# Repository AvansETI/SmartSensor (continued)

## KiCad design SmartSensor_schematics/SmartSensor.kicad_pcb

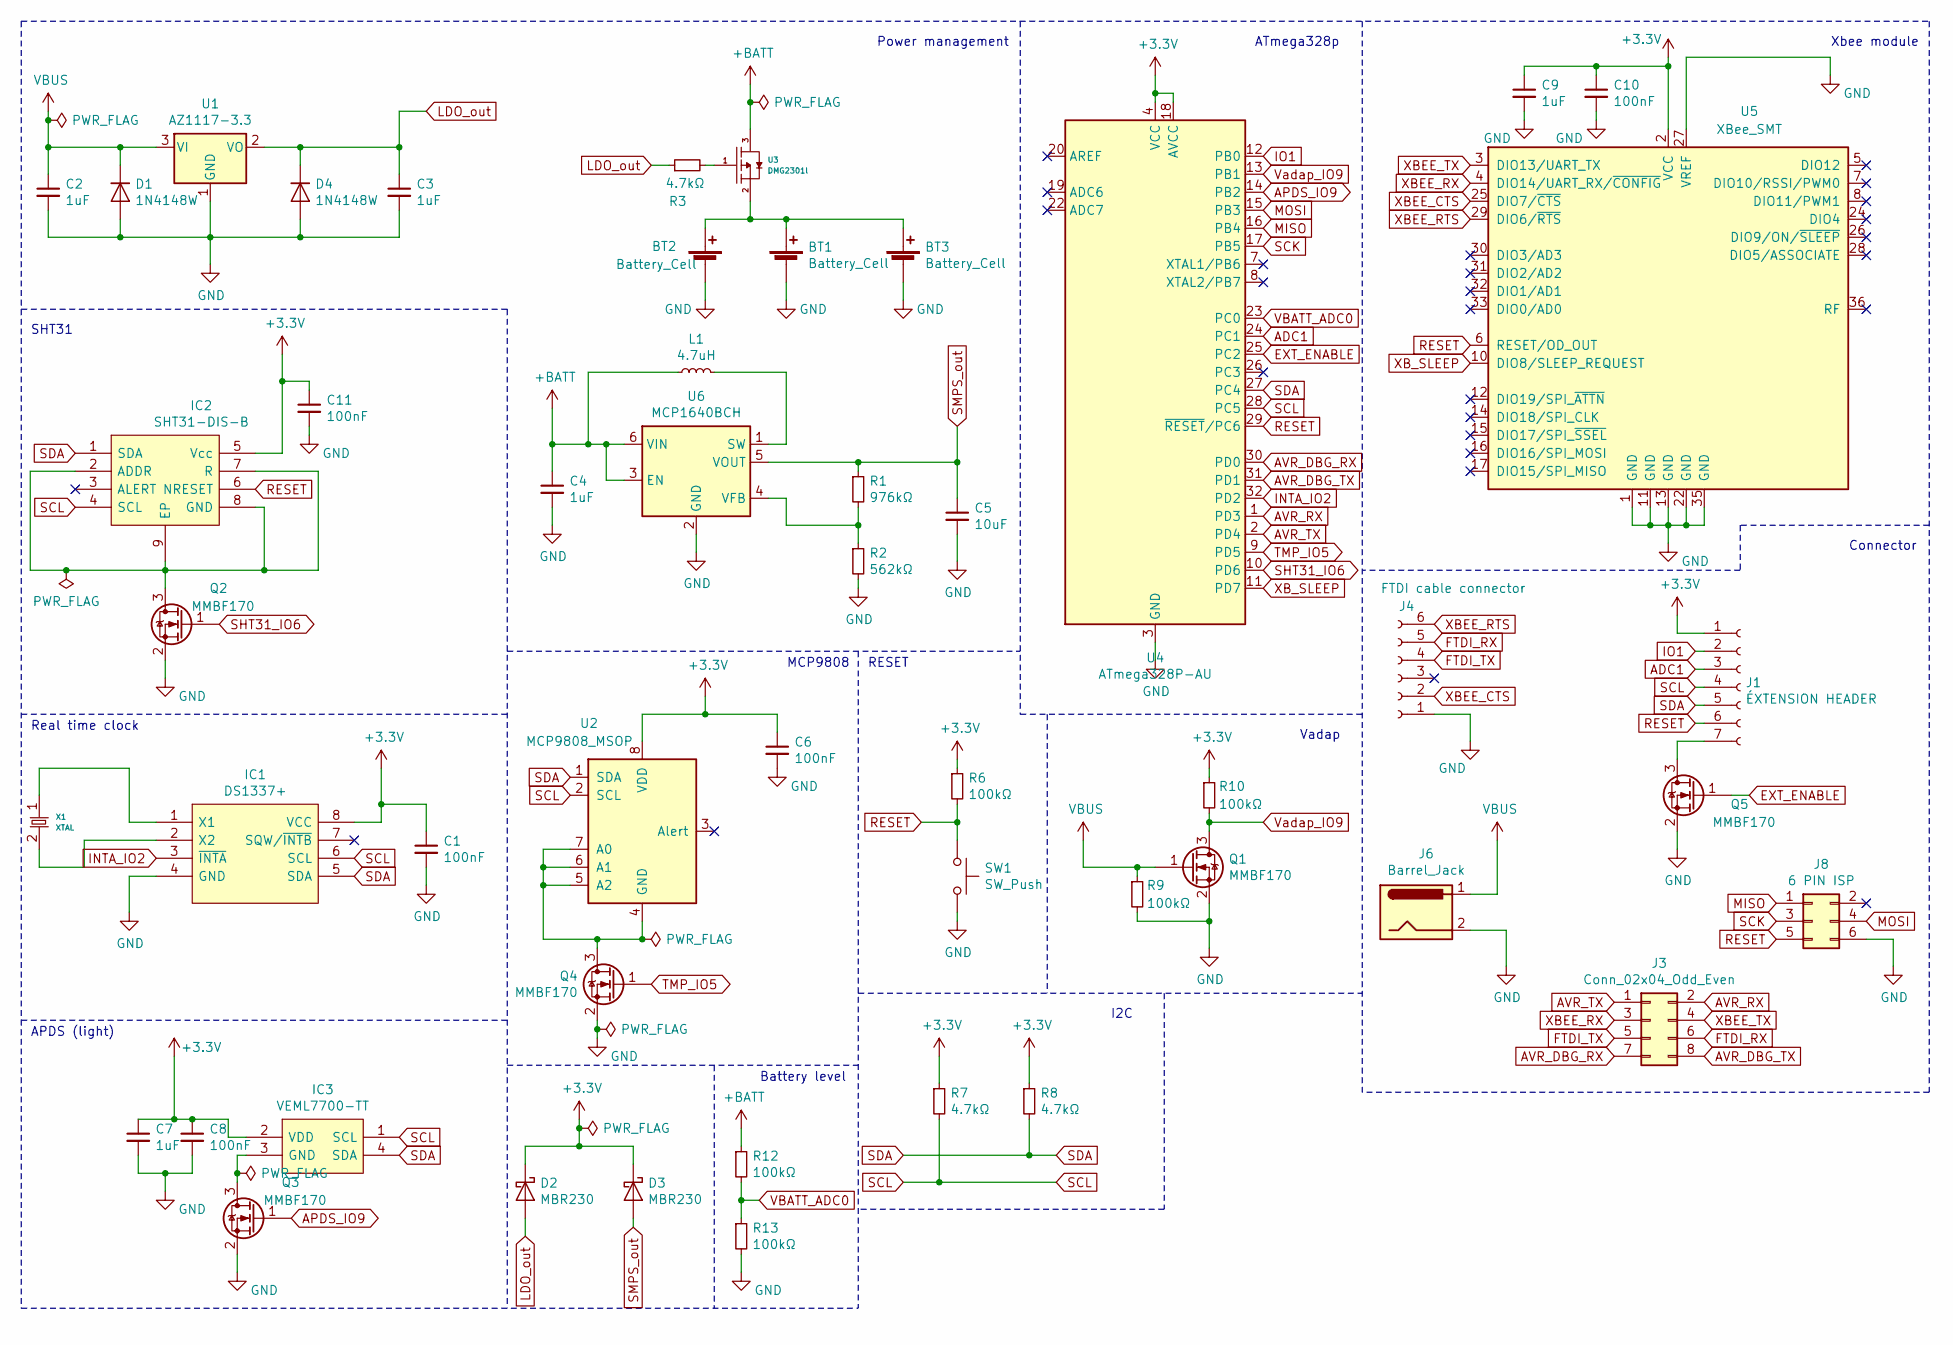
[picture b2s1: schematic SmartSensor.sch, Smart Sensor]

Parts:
BT1, BT2, BT3: Battery_Cell; 2460
C1, C6, C8, C10, C11: 100nF; C_1206_3216Metric_Pad1.42x1.75mm_HandSolder
C2, C3, C4, C7, C9: 1uF; C_1206_3216Metric_Pad1.42x1.75mm_HandSolder
C5: 10uF; C_1206_3216Metric_Pad1.42x1.75mm_HandSolder
D1, D4: 1N4148W; D_SOD-123
D2, D3: MBR230; D_SOD-123F
IC1: DS1337+; DIP794W56P254L938H457Q8N; Manufacturer_Part_Number DS1337+; Mouser Part Number 700-DS1337
IC2: SHT31-DIS-B; SON50P250X250X90-9N-D; Mouser Part Number 403-SHT31-DIS-B
IC3: VEML7700-TT; VEML7700; Manufacturer_Part_Number VEML7700-TT; Mouser Part Number 78-VEML7700-TT
J1: ÉXTENSION HEADER; PinSocket_1x07_P2.54mm_Vertical
J3: Conn_02x04_Odd_Even; PinHeader_2x04_P2.54mm_Vertical
J4: FTDI cable connector; PinHeader_1x06_P2.54mm_Vertical
J6: Barrel_Jack; BarrelJack_Wuerth_6941xx301002
J8: 6 PIN ISP; PinHeader_2x03_P2.54mm_Vertical
L1: 4.7uH; L_Coilcraft_XxL4040
Q1, Q2, Q3, Q4, Q5: MMBF170; SOT-23
R1: 976kΩ; R_1206_3216Metric_Pad1.42x1.75mm_HandSolder
R2: 562kΩ; R_1206_3216Metric_Pad1.42x1.75mm_HandSolder
R3, R7, R8: 4.7kΩ; R_1206_3216Metric_Pad1.42x1.75mm_HandSolder
R6, R9, R10, R12, R13: 100kΩ; R_1206_3216Metric_Pad1.42x1.75mm_HandSolder
SW1: SW_Push; SW_PUSH_6mm
U1: AZ1117-3.3; SOT-223-3_TabPin2
U2: MCP9808_MSOP; MSOP-8_3x3mm_P0.65mm
U3: DMG2301l; SOT-23
U4: ATmega328P-AU; TQFP-32_7x7mm_P0.8mm
U5: XBee_SMT; Digi_XBee_SMT
U6: MCP1640BCH; SOT-23-6
X1: XTAL; Crystal_C38-LF_D3.0mm_L8.0mm_Vertical

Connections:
+3V3: C1.1, C6.1, C7.1, C8.1, C9.1, C10.1, C11.1, D2.1 (K), D3.1 (K), IC1.8 (VCC), IC2.5 (Vcc), IC3.2 (VDD), J1.1, R6.1, R7.1, R8.1, R10.1, U2.8 (VDD), U4.4 (VCC), U4.6 (VCC), U4.18 (AVCC), U5.2 (VCC); also elsewhere on the board
+BATT: C4.1, L1.1, R12.1, U3.3, U6.3 (EN), U6.6 (VIN)
APDS_IO9: Q3.1 (G), U4.14 (PB2); also elsewhere on the board
EXT_ENABLE: Q5.1 (G), U4.25 (PC2); also elsewhere on the board
GND: BT1.2 (-), BT2.2 (-), BT3.2 (-), C1.2, C2.2, C3.2, C4.2, C5.2, C6.2, C7.2, C8.2, C9.2, C10.2, C11.2, D1.2 (A), D4.2 (A), IC1.4 (GND), J4.1, J6.2, J8.6, Q1.2 (S), Q2.2 (S), Q3.2 (S), Q4.2 (S), Q5.2 (S), R2.2, R9.2, R13.2, SW1.2, U1.1 (GND), U4.3 (GND), U4.5 (GND), U4.21 (GND), U5.1 (GND), U5.11 (GND), U5.13 (GND), U5.22 (GND), U5.27 (VREF), U5.35 (GND), U6.2 (GND); also elsewhere on the board
INTA_IO2: IC1.3 (~INTA), U4.32 (PD2); also elsewhere on the board
LDO_out: C3.1, D2.2 (A), D4.1 (K), R3.1, U1.2 (VO)
MISO: J8.1, U4.16 (PB4); also elsewhere on the board
MOSI: J8.4, U4.15 (PB3); also elsewhere on the board
unnamed: BT1.1 (+), BT2.1 (+), BT3.1 (+), U3.2
unnamed: IC1.1 (X1), X1.1
unnamed: IC1.2 (X2), X1.2
unnamed: IC2.2 (ADDR), IC2.7 (R), IC2.8 (GND), IC2.9 (EP), Q2.3 (D)
unnamed: IC3.3 (GND), Q3.3 (D)
unnamed: J1.2, U4.12 (PB0)
unnamed: J1.3, U4.24 (PC1)
unnamed 26: J1.7, Q5.3 (D); also elsewhere on the board
unnamed: J3.1, U4.2 (PD4)
unnamed: J3.2, U4.1 (PD3)
unnamed: J3.5, J4.4
unnamed: J3.6, J4.5
unnamed: J3.7, U4.30 (PD0)
unnamed: J3.8, U4.31 (PD1)
unnamed: L1.2, U6.1 (SW)
unnamed: Q4.3 (D), U2.4 (GND), U2.5 (A2), U2.6 (A1), U2.7 (A0)
unnamed: R1.2, R2.1, U6.4 (VFB)
unnamed: R3.2, U3.1
RESET: IC2.6 (NRESET), J1.6, J8.5, R6.2, SW1.1, U4.29 (~RESET~/PC6), U5.6 (RESET/OD_OUT); also elsewhere on the board
SCK: J8.3, U4.17 (PB5); also elsewhere on the board
SCL: IC1.6 (SCL), IC2.4 (SCL), IC3.1 (SCL), J1.4, R7.2, U2.2 (SCL), U4.28 (PC5); also elsewhere on the board
SDA: IC1.5 (SDA), IC2.1 (SDA), IC3.4 (SDA), J1.5, R8.2, U2.1 (SDA), U4.27 (PC4); also elsewhere on the board
SHT31_IO6: Q2.1 (G), U4.10 (PD6); also elsewhere on the board
SMPS_out: C5.1, D3.2 (A), R1.1, U6.5 (VOUT)
TMP_IO5: Q4.1 (G), U4.9 (PD5); also elsewhere on the board
VBATT_ADC0: R12.2, R13.1, U4.23 (PC0); also elsewhere on the board
VBUS: C2.1, D1.1 (K), J6.1, Q1.1 (G), R9.1, U1.3 (VI)
Vadap_IO9: Q1.3 (D), R10.2, U4.13 (PB1); also elsewhere on the board
XBEE_CTS: J4.2, U5.25 (DIO7/~CTS); also elsewhere on the board
XBEE_RTS: J4.6, U5.29 (DIO6/~RTS); also elsewhere on the board
XBEE_RX: J3.3, U5.4 (DIO14/UART_RX/~CONFIG); also elsewhere on the board
XBEE_TX: J3.4, U5.3 (DIO13/UART_TX); also elsewhere on the board
XB_SLEEP: U4.11 (PD7), U5.10 (DIO8/SLEEP_REQUEST); also elsewhere on the board

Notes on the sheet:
Xbee module
RESET
Real time clock
MCP9808
SHT31
I2C
ATmega328p
APDS (light)
Vadap
Battery level
Connector
Power management

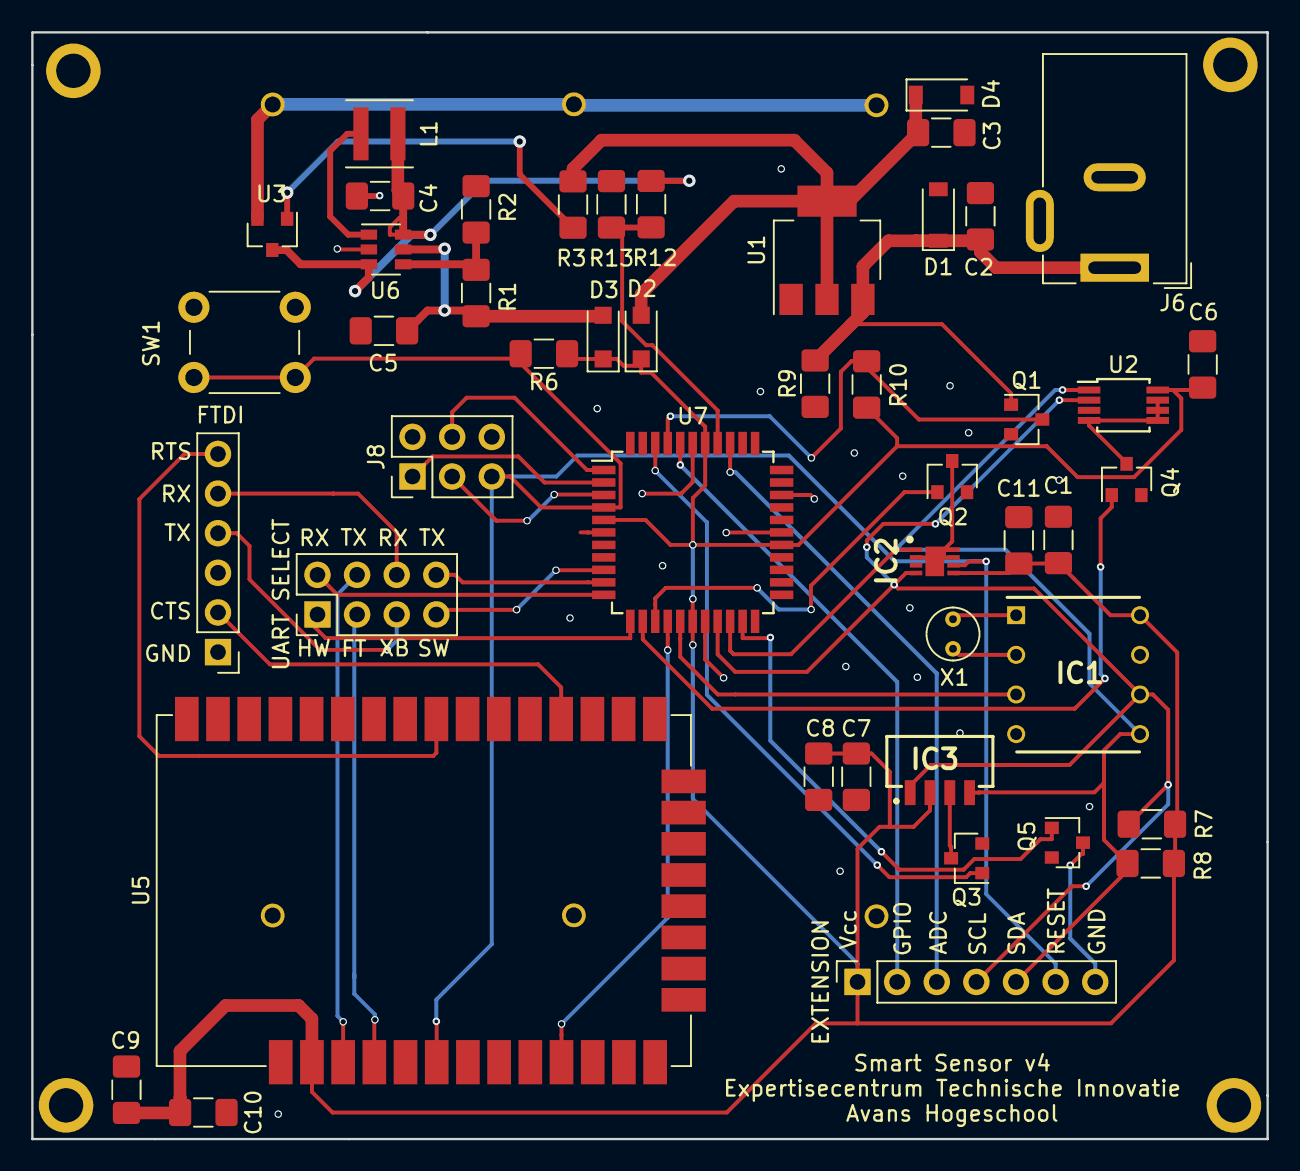
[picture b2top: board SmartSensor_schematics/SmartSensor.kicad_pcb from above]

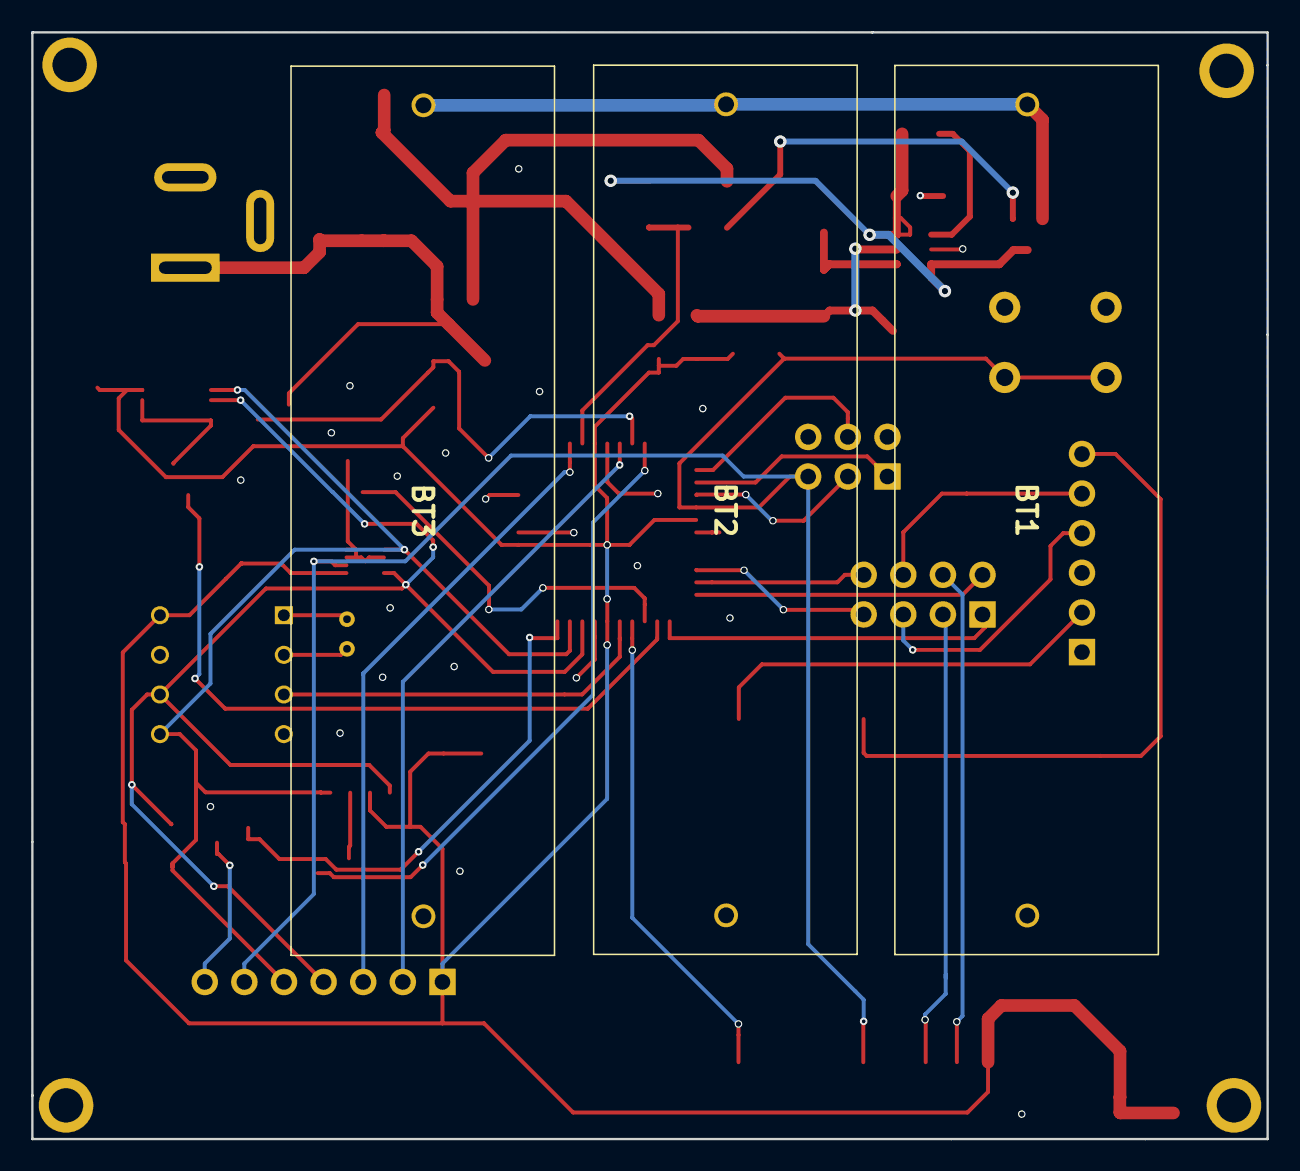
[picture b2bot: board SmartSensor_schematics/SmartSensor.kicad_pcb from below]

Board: 2 copper layers, 79.2 x 70.9 mm, 54 parts (3 on the bottom side), 42 nets.

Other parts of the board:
EXTENSION: ÉXTENSION HEADER; PinSocket_1x07_P2.54mm_Vertical
FTDI: FTDI cable connector; PinHeader_1x06_P2.54mm_Vertical
REF1, REF2, REF3, REF4: MountingHole_2.2mm_M2_ISO7380_Pad
U7: ATmega1284P-AU; TQFP-44_10x10mm_P0.8mm
UART SELECT: Conn_02x04_Odd_Even; PinHeader_2x04_P2.54mm_Vertical

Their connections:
+3V3: EXTENSION.1, U7.5, U7.17, U7.27, U7.38; also elsewhere on the board
ADC1: EXTENSION.3, U7.36
APDS_IO9: U7.42; also elsewhere on the board
AVR_DBG_RX: U7.9, UART SELECT.7
AVR_DBG_TX: U7.10, UART SELECT.8
AVR_RX: U7.11, UART SELECT.2
AVR_TX: U7.12, UART SELECT.1
EXT_ENABLE: U7.21; also elsewhere on the board
FTDI_RX: FTDI.5, UART SELECT.6
FTDI_TX: FTDI.4, UART SELECT.5
GND: FTDI.1, U7.6, U7.18, U7.28, U7.39; also elsewhere on the board
INTA_IO2: U7.16; also elsewhere on the board
IO1: EXTENSION.2, U7.40
MISO: U7.2; also elsewhere on the board
MOSI: U7.1; also elsewhere on the board
unnamed 26: EXTENSION.7; also elsewhere on the board
RESET: EXTENSION.6, U7.4; also elsewhere on the board
SCK: U7.3; also elsewhere on the board
SCL: EXTENSION.4, U7.19; also elsewhere on the board
SDA: EXTENSION.5, U7.20; also elsewhere on the board
SHT31_IO6: U7.14; also elsewhere on the board
TMP_IO5: U7.13; also elsewhere on the board
VBATT_ADC0: U7.37; also elsewhere on the board
Vadap_IO9: U7.41; also elsewhere on the board
XBEE_CTS: FTDI.2; also elsewhere on the board
XBEE_RTS: FTDI.6; also elsewhere on the board
XBEE_RX: UART SELECT.3; also elsewhere on the board
XBEE_TX: UART SELECT.4; also elsewhere on the board
XB_SLEEP: U7.15; also elsewhere on the board

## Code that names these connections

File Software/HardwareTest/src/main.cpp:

/*
 * SmartSensor main
 * 
 * @author Michel Megens
 * @email  michel@michelmegens.net
 * @author Maurice Snoeren
 * @email  mac.snoeren@avans.nl
 */

#include <stdlib.h>
#include <Arduino.h>

#include <HDC1080.h>
#include <XBee.h>
#include <Adafruit_VEML7700.h>
#include <SmartSensor.h>

void loop()
{
	auto sensor = smartsensor::Application::Instance();

	sensor->enableHumiditySensor();
	sensor->enableLightSensor();
	sensor->enableXBee();
	sensor->sleepXBee(HIGH);

	delay(800); // Sample time

	sensor->measureAndSend();

	delay(2000);
}

void test()
{
}

static void setupHAT()
{
    pinMode(HAT_AIO1, INPUT);
    pinMode(HAT_AIO2, INPUT);
    pinMode(HAT_AIO3, INPUT);
    pinMode(HAT_AIO4, INPUT);
    pinMode(HAT_AIO5, INPUT);
    pinMode(HAT_AIO6, INPUT);

    pinMode(HAT_DIO1, INPUT);
    pinMode(HAT_DIO2, INPUT);
    pinMode(HAT_DIO3, INPUT);
    pinMode(HAT_DIO4, INPUT);
    pinMode(HAT_DIO5, INPUT);
    pinMode(HAT_DIO6, INPUT);
    pinMode(HAT_DIO7, INPUT);
    pinMode(HAT_DIO31, INPUT);
}

// Configure the Atmega according the hardware design!
void setup()
{
	Serial.begin(9600, SERIAL_8N1);
	SPI.begin();
	Wire.begin();

    pinMode(VBAT_ADC0, INPUT);  //Battery measurement
    pinMode(INTA_ADC3, OUTPUT); // Realtime clock: /INTA
    //digitalWrite(INTA_ADC3, LOW); // ??

    pinMode(HDC1080_IO6, OUTPUT);   // HDC1080 Humidity/Temp On/Off
    digitalWrite(HDC1080_IO6, LOW); // Switch HDC1080 default off

    pinMode(LED_IO8, OUTPUT);
    pinMode(Vadap_IO9, INPUT); // When adapter is plugged in 5V (Does it work?)
    
    pinMode(XBEE_SLEEP, OUTPUT);

    pinMode(XBEE_ON_OFF, OUTPUT); // XBee module

    pinMode(AVR_RX, INPUT); // Soft UART??
    pinMode(AVR_TX, OUTPUT); // ??

    pinMode(VEML7700_IO5, OUTPUT); // Light sensor

	auto instance = smartsensor::Application::Instance();
	instance->begin();

    setupHAT();
}

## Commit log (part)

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2021-04-06 Added a node version
2021-04-07 Added gitignore
2021-04-19 Now compiling with full warnings, fixed all warnings except for those generated by FreeRTOS. The compiler doesn't support [[fallthrough]] or [[gnu::fallthrough]] so __attribute__ ((fallthrough)) is u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
2021-04-28 Development progress
2021-04-29 Added a driver for the THS. Also fixed bugs in the TWI workflow.
2021-04-30 fixed the conversion calculation. Added a multi sample measurement.
2021-04-30 development
2021-05-16 Added reconnection of the MQTT broker to the sim client and server
2021-06-01 Added token
2021-06-10 Added timestamp to the measurements, so devices with a wrong time are also able to connect
2021-06-10 Fixed the time disruption bug
2021-06-16 Added final version 1.2 to the repository
2021-06-16 Bump ws from 7.4.4 to 7.4.6 in /SmartNetwork/smart-server
    Bumps [ws](https://github.com/websockets/ws) from 7.4.4 to 7.4.6.
    - [Release notes](https://github.com/websockets/ws/releases)
    - [Commits](https://github.com/websockets/ws/compare/7.4.4...7.4.6)
    ---
    updated-dependencies:
    - dependency-name: ws
2021-06-16 Renamed the python software for the smartnetwork, so everything is okay again.
2021-09-06 Added boards to the smart-sensor folder and included installation info
2021-09-07 Added version of the hardware and firmware to the serial
2021-09-08 More comments and it works now except the Wemos.
2021-09-10 Added flashing led wemos
2021-09-10 Updated driver and added SHTC3Driver to the wished design
2021-09-10 Finalized the IDriver, Driver and SHTC3Driver. Added getID() from the SHT and a correct setup.
2021-09-11 Added a template for the MCP7940Driver to add the RTC to the play.
2021-09-11 Not yet finisched MPC7940N RTC chip driver, defined the TODO's
2021-09-11 Moved the BCD functions to the more generic class
2021-09-11 Removed the SmartSensor board, that is not required! Changed the platform.io configuration
2021-09-11 Added an improved gitignore file
2021-09-11 Removed files that are in the gitignore!
2021-09-11 Started the board approach. It is still required to fill in the base board class that abstracts all the hardware.
2021-09-12 Add the setup of the MFP pin as input
2021-09-12 Added millis to the loop and callback when drivers have measurements. millis not implemented in the background yet
2021-09-12 Memory optimisation and added some millis approach using timer1
2021-09-12 Placed all string in the flash and removed usage of RAM significantly
2021-09-12 Added Serial singleton class, still blocking, but have an idea
2021-09-13 Moved Timer1Driver to Timer1 util and add interface to MeasurementBuffer
2021-09-13 Added experiment SHTC3 reading that works correctly!
2021-09-13 Moved I2C and created an idea to have an interrupts based I2C management. Implemented SHTC3 for this.
2021-09-13 Implemented RTC event, so when the timestamp is available, the measurements can be sent.
2021-09-16 Added documentation for common issues
    Will keep updating document when further issues and solutions are found
2021-09-16 Small edits for easier readability
    Switched from USB to serial converter to Arduino
2021-09-16 Added additional note about incorrect date
2021-09-22 Progress on VEML7700 driver
    No proper data recieved yet, possibly wrong read port
2021-09-23 Changing data recieved, figuring out how to properly gather
2021-09-23 Temporarily removed LED loop to better test Lux sensor
2021-09-23 Data is gathered, figuring out conversions
2021-09-23 Added TODOs
2021-09-23 Updated TODOs
2021-09-23 Added standard config to VEML7700
2021-09-30 Attempting to read gain from device
2021-09-30 Currently the CHANGEGAIN function affects shutdown, TEMP until gain fix
2021-10-04 Added a bootloader
2021-10-07 Problem wasn't in read, but in write, problem persists
2021-10-07 Seperating functions helped with write, TODO fix read
2021-10-07 Writing wasn't working due to an unneeded edit, now read and write work
2021-10-14 Progress, shutdown does not work properly yet
2021-10-14 readGain now only reads Gain, further functions should be easily writable
2021-10-14 Progress, gain currently overwrites
2021-10-14 Gain currently still not functioning
2021-10-14 Methods function correctly with test print
2021-10-16 Added I2C.h with all the generics
2021-10-17 Created the bootloader code
2021-10-18 Implemented the new I2C task and changed the SHTC3 and RTC
2021-10-22 Attemtp on bootloader with earlier code
2021-10-22 Progress on bootloader
2021-10-23 Changed main comments
2021-10-23 Added watchdog of 8 seconds
2021-10-23 Development progress...
2021-10-24 Made the last changes on updating the documentation and memory footprint.
2021-10-24 Added reset cause to check if a watchdog reset happened.
2021-10-24 Added loop timing. Found bug in sampling of SHTC3
2021-10-27 Development progress. XBee installed check and read standard values.
2021-10-27 XBee works in transparent mode, should be in API later
2021-10-28 A working test example to recieve the data packets from XBee
2021-10-29 Decode revieving packet 0x90 from the XBEE.
2021-10-29 Enlarged the serial buffers to 50 and add an async call, everything is async again
2021-10-30 Added documentation README.md file
2021-10-30 Added a new documentation scheme to the repo.
2021-10-30 Fixed the location of the images.
2021-11-11 Temp Commit
2021-11-11 Large cleanup for smaller size
2021-11-11 Attempt to let bootloader interact with other memory
2021-11-18 Bootloader does not function properly, jump does not work properly
2021-11-25 Regular program should not delete bootloader anymore
2021-11-28 Added a first version to send smartmeter data to the smartnetwork
2021-11-28 Made some changes to get stable software
2021-11-28 Changed the mode of the files to executable
2021-12-01 Fixed bug in def alert
2021-12-02 Slight changes to bootloader for command testing
2021-12-02 Switching between states, working on readability
2021-12-05 Fixed softsensor openweatherdata and added clean.py
2021-12-06 Fixed the configuration exposure and started with the forecastsolar api
2021-12-06 Fixed bug and finalized the forecast application
2021-12-07 Added documentation
2021-12-09 Optimizations for hex file transfer, delay needed
2021-12-12 Finalizing the SmartNetwork software
2021-12-14 Added comments and version information to the files.
2021-12-16 Small edit to jump
2021-12-16 Commands now only work when entered in 1 go
2021-12-20 First version that works until implementation of the protocol.
2021-12-27 Added configuration and ECC functionality
2021-12-28 A working version of mode 1 with ECC key exchange
2021-12-28 Added debugging feature to processing
2021-12-29 Finalized node/init and shared_key is succefully read from the DB
2021-12-29 Fixed some bugs, only signature check needs to be implemented
2022-01-06 Finalized the test and gas is in it
2022-01-08 Refactoring and added messages for measurements and commands.
2022-01-08 Added sendInitMessage to send the init message
2022-01-09 Finalized the code with co2 and light
2022-01-09 Not really required and not finished!
2022-01-12 Finalized the beta version of the wifi wemos gateway
2022-01-13 Small edits during conversion
2022-01-13 develpoment progress
2022-01-13 Added config files
2022-01-13 Changed sampling strategy that is more synchronized among all drivers.
2022-01-13 Added comments and removed some code and print statements
2022-01-15 Solved bug, timer 1 interfering with CO2 out pint, moved to timer 4.
2022-01-20 Massive amount of RAM usage in commented function, attempting to fix
2022-01-20 Other program successfully uploaded using python script
    Developing different program for easy demo
2022-01-20 Issues with Python Script
2022-01-23 Changed the id and fixed the bug that restarted the MCU
2022-01-25 Continuing Issues with multi-page programming
2022-01-26 Small progress on multi-page programming
2022-01-26 Issue most likely located within prog array
2022-01-26 Issue determined to lie in fuses
2022-01-26 Issue most likely caused by upload protocol investigating further
2022-01-26 Fuse issue not yet resolved
2022-01-27 Fuses were reversed
2022-01-27 Issues persisting, character recieval broken
2022-01-27 Issue determined not to be baud rate
2022-01-27 Testing earlier version
2022-01-27 Returning to multi-page fix
2022-01-27 For some reason first line of script gives extra chars
2022-01-27 Issue lies within prog array, only values of 255
2022-01-27 Temp move away for demo
2022-02-10 Basic Serial function, sendstring not working, for now sufficient
2022-02-11 Serial fixed, working on moving state machine to proper class
2022-02-17 Issues with state machine
2022-02-22 Bootloader now cycles, small issue with check
2022-03-10 Improvements to state machine and python script
2022-03-14 Communication issues fixed, adding comments
2022-03-17 Final update for communication demo
2022-03-22 Interrupt currently present, working on functional removal
2022-03-22 Interrupt removed, working on functions
2022-03-24 UPdate for cleaner communication
2022-03-24 Finished communication for demo
2022-03-29 Work on write class
2022-03-31 Small improvements on communication, working on write
2022-03-31 Progress on write, currently non-functional
2022-04-01 Small change for demo
2022-04-05 Data itself is not the issue, issue lies within address
2022-04-07 progress on write, data arrives correctly, issue with offset
2022-04-07 Fixed offset issue
2022-04-07 File upload successful, working on jump to main program
2022-04-14 Removed unneeded part of boot
2022-04-21 add comments to h file and finish h file
2022-04-21 add message interface to max4466 driver
2022-04-21 added some comments to h file
2022-04-26 Add ADC
2022-04-28 Bump node-fetch from 2.6.1 to 2.6.7 in /SmartNetwork/smart-server
    Bumps [node-fetch](https://github.com/node-fetch/node-fetch) from 2.6.1 to 2.6.7.
    - [Release notes](https://github.com/node-fetch/node-fetch/releases)
    - [Commits](https://github.com/node-fetch/node-fetch/compare/v2.6.1...v2.6.7)
    ---
    updated-dependencies:
    - dependency-name: node-fetch
2022-04-28 Small changes to communication and main
2022-04-28 [ADD] AnalogDriver class. This is a class that facilitates functionality for drivers that read from an analog pin. It extends the Driver class and this functionality can be added with the late_ metho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
2022-05-10 removed more files
2022-05-12 PotMeter Setup
    Attempt at making potmeter driver - ADC not complete
2022-05-12 AnalogDriver implementation of Pot Meter
    rebased on new AnalogDriver class
2022-05-17 comment
2022-05-17 added API frame construction
2022-05-17 added zigbee messages, needs to be integrated into state machine
2022-05-19 made zigbee separate interface
2022-05-24 dafuq 144% ram???
2022-05-24 use xbee again
2022-05-24 xbee
2022-05-31 add todo comment
2022-06-02 temp push
2022-06-02 add extra options for zigbee message
2022-06-07 Revert "pointers suck"
    This reverts commit 877d4431a3e54c57d97fec9dc193fa7b55d1dfe1.
2022-06-09 Added xbee message deliverer to potmeterdriver
2022-06-09 Finished sending messages trough zigbee
2022-06-09 finish init msg
2022-06-09 progress
2022-06-14 added wait on publish, messages still not coming through however :(
2022-06-14 add sound to measurements
2022-06-14 Testing images and lower framerate
2022-06-16 wait on send init msg
2022-06-16 remove useless variable
2022-06-16 switch
2022-06-16 bruh
2022-06-21 Finally fix sending MQTT, the problem was that the timestamp was invalid
2022-06-21 it crash :(
2022-06-21 increase delays for sending measurements
2022-06-29 Simple demo
2022-07-11 Added forwarder
2022-10-05 Fixes and bugfixes
2022-10-05 Removed the credentials in the code.
2022-11-10 Made the required changes to make it more robust
2022-12-05 Checking for the correct source code again.
2022-12-05 Final merge
